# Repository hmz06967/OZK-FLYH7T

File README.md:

# OZK-FLYH7T
Eagle design witdh STM32H750x BGA flycontroller board support arduplot and betaflight tested OK but R12 no connect Vbat and can be add to boot button Just has a TP and Vbus not connected to +5V.

## Ekran Görüntüleri

[Canlı yazılım testi](https://www.youtube.com/watch?v=nz5CqahaaQQ)

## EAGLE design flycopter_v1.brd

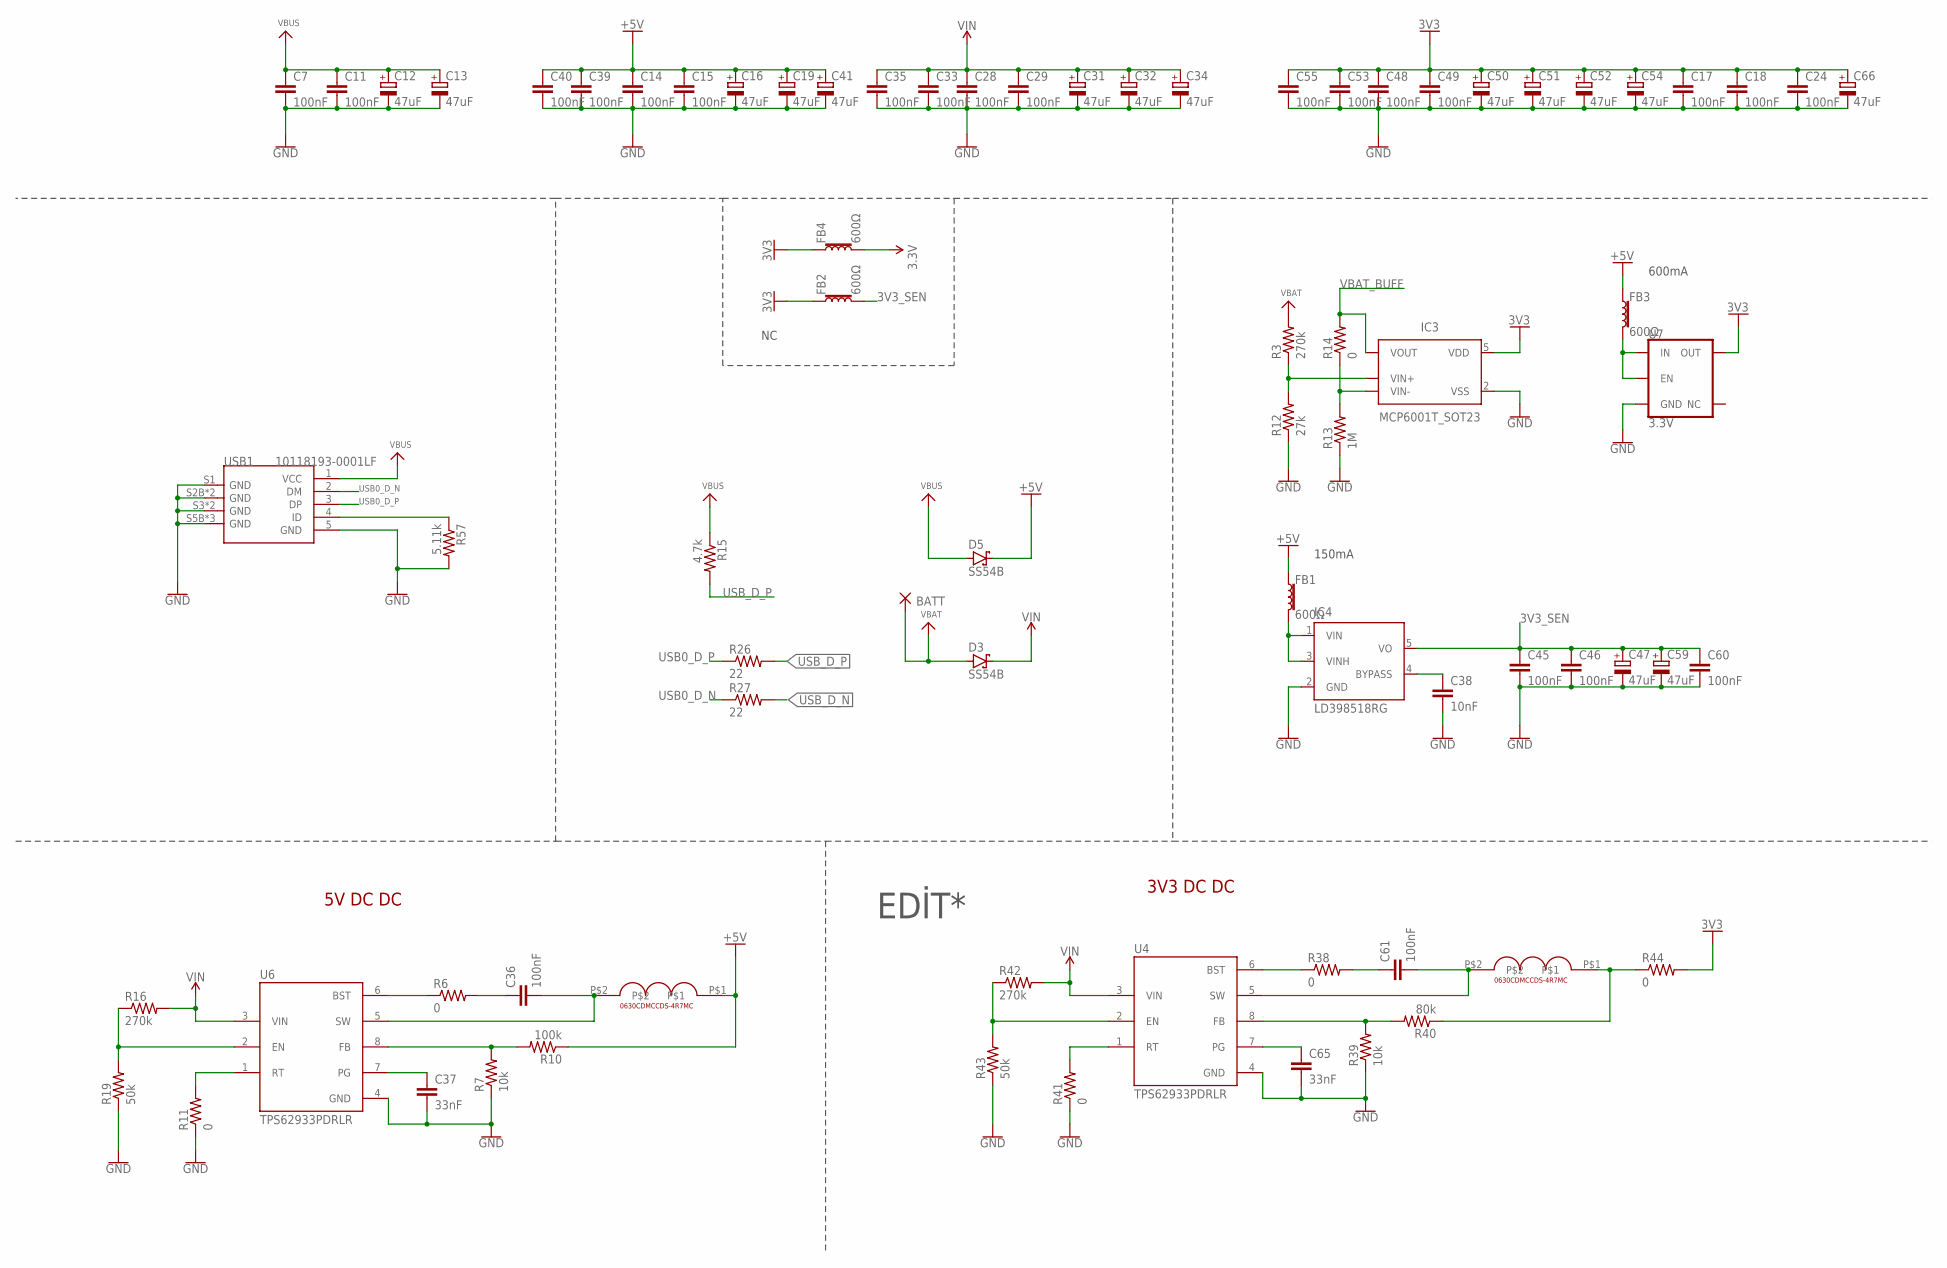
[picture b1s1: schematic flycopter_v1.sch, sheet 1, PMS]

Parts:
BATT: SMD5; SMD2,54-5,08
C7, C11, C14, C15, C17, C18, C24, C28, C29, C33, C35, C36, C39, C40, C45, C46, C48, C49, C53, C55, C60, C61: 100nF; C0603K
C12, C13, C16, C19, C31, C32, C34, C41, C47, C50, C51, C52, C54, C59, C66: 47uF; A/3216-18R
C37, C65: 33nF; C0603K
C38: 10nF; C0603K
D3, D5: SS54B; SMB
FB1, FB2, FB3, FB4: 600Ω; 0805
IC3: MCP6001T_SOT23; SOT95P280X145-5N
IC4: LD398518RG; TSOT23-5L
R3, R16, R42: 270k; R0402
R6, R11, R14, R38, R41: 0; R0402
R7, R39: 10k; R0402
R10: 100k; R0402
R12: 27k; R0402
R13: 1M; R0402
R15: 4.7k; R0402
R19, R43: 50k; R0402
R26, R27: 22; R0402
R40: 80k; R0402
R44: 0; M0805
R57: 5.11k; R0402
U4, U6: TPS62933PDRLR; SOFL50P160X60-8N
U7: 3.3V; SOT23-5
U$5: 6.8uH; 0630CDMCCDS-4R7MC
U$9: 4.7uH; 0630CDMCCDS-4R7MC
USB1: 10118193-0001LF; MICRO-USB5+6P-SMD-0.65-B

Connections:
3.3V: FB4.2; also elsewhere on the board
3V3: C17.1, C18.1, C24.1, C48.1, C49.1, C50.+, C51.+, C52.+, C53.1, C54.+, C55.1, C66.+, FB2.1, FB4.1, IC3.5 (VDD), R44.2, U7.5 (OUT); also elsewhere on the board
3V3_SEN: C45.1, C46.1, C47.+, C59.+, C60.1, FB2.2, IC4.5 (VO); also elsewhere on the board
+5V: C14.1, C15.1, C16.+, C19.+, C39.1, C40.1, C41.+, D5.C, FB1.1, FB3.1, R10.1, U$5.P$1; also elsewhere on the board
GND: C7.2, C11.2, C12.-, C13.-, C14.2, C15.2, C16.-, C17.2, C18.2, C19.-, C24.2, C28.2, C29.2, C31.-, C32.-, C33.2, C34.-, C35.2, C37.2, C38.2, C39.2, C40.2, C41.-, C45.2, C46.2, C47.-, C48.2, C49.2, C50.-, C51.-, C52.-, C53.2, C54.-, C55.2, C59.-, C60.2, C65.2, C66.-, IC3.2 (VSS), IC4.2 (GND), R7.1, R11.1, R12.1, R13.1, R19.1, R39.1, R41.1, R43.1, R57.2, U4.4 (GND), U6.4 (GND), U7.2 (GND), USB1.5 (GND), USB1.S1 (GND), USB1.S2B (GND), USB1.S2T (GND), USB1.S3 (GND), USB1.S4 (GND), USB1.S5B (GND), USB1.S5T (GND), USB1.S6 (GND); also elsewhere on the board
unnamed: C36.2, U6.5 (SW), U$5.P$2
unnamed: C36.1, R6.2
unnamed: R6.1, U6.6 (BST)
unnamed: R7.2, R10.2, U6.8 (FB)
unnamed: C37.1, U6.7 (PG)
unnamed: R16.1, R19.2, U6.2 (EN)
unnamed: R11.2, U6.1 (RT)
unnamed: FB1.2, IC4.1 (VIN), IC4.3 (VINH)
unnamed: C38.1, IC4.4 (BYPASS)
unnamed: FB3.2, U7.1 (IN), U7.3 (EN)
unnamed: IC3.4 (VIN-), R13.2, R14.1
unnamed: IC3.3 (VIN+), R3.1, R12.2
unnamed: C61.2, U4.5 (SW), U$9.P$2
unnamed: R57.1, USB1.4 (ID)
unnamed: C61.1, R38.2
unnamed: R38.1, U4.6 (BST)
unnamed: R39.2, R40.2, U4.8 (FB)
unnamed: C65.1, U4.7 (PG)
unnamed: R41.2, U4.1 (RT)
unnamed: R42.1, R43.2, U4.2 (EN)
unnamed: R40.1, R44.1, U$9.P$1
USB0_D_N: R27.1, USB1.2 (DM)
USB0_D_P: R26.1, USB1.3 (DP)
USB_D_N: R27.2; also elsewhere on the board
USB_D_P: R15.2, R26.2; also elsewhere on the board
VBAT: BATT.1, D3.A, R3.2
VBAT_BUFF: IC3.1 (VOUT), R14.2; also elsewhere on the board
VBUS: C7.1, C11.1, C12.+, C13.+, D5.A, R15.1, USB1.1 (VCC)
VIN: C28.1, C29.1, C31.+, C32.+, C33.1, C34.+, C35.1, D3.C, R16.2, R42.2, U4.3 (VIN), U6.3 (VIN)

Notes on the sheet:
150mA
600mA
EDİT*
5V DC DC
3V3 DC DC

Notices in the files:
parts and their libraries:
SparkFun-RF: Licensing: Creative Commons ShareAlike 4.0 International - https://creativecommons.org/licenses/by-sa/4.0
